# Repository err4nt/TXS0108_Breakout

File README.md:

# TXS0108_Breakout
Breakout for the TXS0108e

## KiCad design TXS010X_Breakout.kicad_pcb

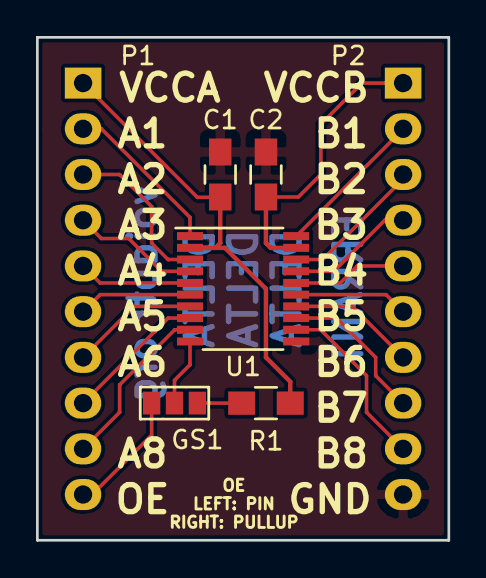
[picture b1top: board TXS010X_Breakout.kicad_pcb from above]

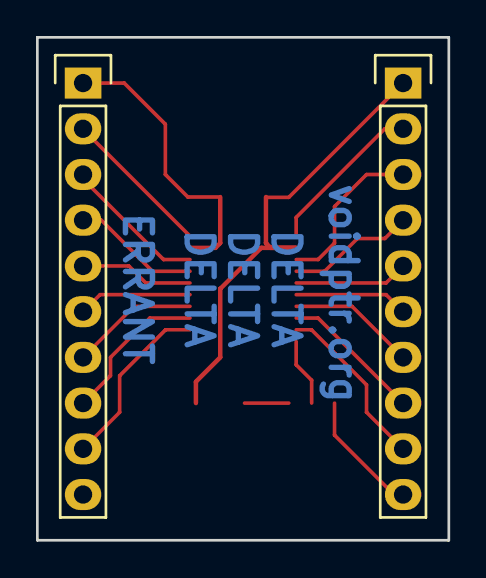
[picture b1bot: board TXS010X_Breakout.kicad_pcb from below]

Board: 2 copper layers, 22.9 x 27.9 mm, 7 parts (2 on the bottom side), 22 nets.

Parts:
C1, C2: 0.1uF; C_0805_HandSoldering
GS1: GS3
P1, P2: CONN_01X10; Pin_Header_Straight_1x10
R1: 0; R_0805_HandSoldering
U1: TXS0108e; TSSOP-20_4.4x6.5mm_Pitch0.65mm

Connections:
GND: C1.1, C2.1, P2.10, U1.11
unnamed: C2.2, P2.1, U1.19
unnamed: GS1.1, P1.10
unnamed: GS1.2, U1.10
unnamed: GS1.3, R1.2
unnamed: P1.2, U1.1
unnamed: P1.3, U1.3
unnamed: P1.4, U1.4
unnamed: P1.5, U1.5
unnamed: P1.6, U1.6
unnamed: P1.7, U1.7
unnamed: P1.8, U1.8
unnamed: P1.9, U1.9
unnamed: P2.2, U1.20
unnamed: P2.3, U1.18
unnamed: P2.4, U1.17
unnamed: P2.5, U1.16
unnamed: P2.6, U1.15
unnamed: P2.7, U1.14
unnamed: P2.8, U1.13
unnamed: P2.9, U1.12
VCC: C1.2, P1.1, R1.1, U1.2

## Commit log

2016-09-23 Rev X1
